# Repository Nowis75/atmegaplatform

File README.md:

# ATmega328P socket-based teaching platform

Firmware examples and supporting material for the paper
*"Design and Implementation of a Jumper-Wire-Free, Socket-Based PCB Platform for Microcontroller Education"* (M. Novak, University of South Bohemia in České Budějovice).

The platform is a two-layer carrier PCB for the ATmega328P (DIP-28, 16 MHz, 5 V). All connections are fixed copper traces. Students insert the functional components into female socket headers: the MCU, crystal, load capacitors, reset network, LEDs, switches and thermistors. No jumper wires are needed.

## Board pin map

| Function | Pins |
|---|---|
| LEDs | D9, D10, D11, D13 (220 Ω series resistors) |
| Switches | D5, D6, D7 (switch to GND, use `INPUT_PULLUP`) |
| NTC thermistor dividers | A0, A1 (10 kΩ NTC to GND, β = 3950; 10 kΩ to VCC) |
| I²C header J1 | VCC, GND, SCL (A5), SDA (A4) |
| UART header UART1 | VCC, GND, RX, TX, DTR, RTS: connect a 5 V CP2102 USB-to-TTL adapter (TX↔RX crossed) |
| Auto-reset | DTR → 1 µF → RESET (automatic reset before upload) |

## Repository structure

```
firmware/
  arduino/      Arduino IDE sketches (open the .ino in each folder)
  platformio/   PlatformIO project, one environment per example
docs/fritzing/  Fritzing wiring diagrams of the exercises (breadboard reference)
hardware/       KiCad schematic and PCB of the carrier board, BOM
data/           Anonymized questionnaire data (to be added)
```

## Programming

The ATmega328P carries an Arduino-compatible (Uno/Optiboot) bootloader. The board connects to the computer through a CP2102 USB-to-TTL adapter, which also powers it from USB.

**Arduino IDE:** select *Arduino Uno* as the board and the CP2102 serial port, then upload.

**PlatformIO / VS Code:**

```bash
cd firmware/platformio
pio run -e 01-led-test -t upload   # build and upload one example
pio device monitor                 # serial monitor, 9600 Bd
```

## Examples

| Topic | Arduino IDE (`firmware/arduino`) | PlatformIO env (`firmware/platformio`) |
|---|---|---|
| Board test, serial | `01-serial-test` | `01-led-test` |
| Digital output | `02-a-led`, `02-b-led-blink` | `01-led-test` |
| Digital input | `02-c-led-button` | `05-a-button-polling` |
| Logic functions | `02-d-logic-gate` | `02-e-logic-function` |
| Serial communication | `03-a-serial-sum`, `03-b-serial-led` | `03-a` … `03-f` |
| EEPROM | `04-eeprom-led` | `04-a-eeprom-led-state`, `04-b-eeprom-sos`, `04-c-eeprom-counter` |
| Interrupts, timers | — | `05-b-button-interrupt`, `05-c-timer-isr` |
| I²C | `06-i2c-vl53l0x` (needs Adafruit_VL53L0X library) | `06-a-i2c-bme280`, `06-b-i2c-scanner` |
| Analog input (NTC) | `07-analog-ntc` | `07-analog-ntc` |

Notes:

- `05-b-button-interrupt` uses external interrupt INT0 on D2, which is not routed to a board switch. Connect a button to D2 or adapt the pin.
- Some PlatformIO examples (`04-*`, `05-a`) were written for breadboard wiring with active-high buttons (`INPUT`, external pull-down). On the PCB, the switches connect to GND. Change these sketches to `INPUT_PULLUP` and test for `LOW`, as the Arduino sketches `02-c-*` already do.

## License

Firmware and hardware design files: MIT (see `LICENSE`).

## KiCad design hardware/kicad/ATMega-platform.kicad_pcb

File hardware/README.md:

# Hardware: carrier PCB (KiCad)

| File | Content |
|---|---|
| `kicad/ATMega-platform.kicad_pro` | KiCad project |
| `kicad/ATMega-platform.kicad_sch` | Schematic |
| `kicad/ATMega-platform.kicad_pcb` | Two-layer PCB layout (1.6 mm) |
| `bom.csv` | Bill of materials |

Gerber and drill files are generated from the `.kicad_pcb` with KiCad's *Fabrication Outputs* (File → Fabrication Outputs → Gerbers / Drill Files).

## Revision notes

- **LED series resistors R2–R5 are 220 Ω.** The first prototype boards used 10 kΩ, which made the LEDs very dim.
- **C3 (1 µF) couples the DTR line of the CP2102 adapter to RESET.** The Arduino IDE / PlatformIO therefore resets the MCU automatically before an upload.
- **The push buttons SW2–SW4 connect D5–D7 to GND.** Use `INPUT_PULLUP` in firmware (pressed = LOW).
- **No dedicated VCC/AVCC decoupling capacitor is fitted.** Adding 100 nF ceramic capacitors at pins 7/8 and 20/22 is recommended for the next revision.
- **The schematic is the current reference (rev. 1.1).** The LED circuits are drawn as MCU pin → 220 Ω → LED → GND. The tactile push buttons SW2–SW4 (6 × 6 mm, symbol `SW_Push`) switch D5–D7 to GND.
- **The `.kicad_pcb` is the layout of the manufactured boards (rev. 1.0).** There the LED sits between the pin and the resistor, the resistor goes to GND, and the silkscreen still shows 10 kΩ for R2–R5. Because all parts are socketed, the boards work with the rev. 1.1 values: insert the LED with its anode toward the MCU pin and use 220 Ω resistors. Run *Tools → Update PCB from Schematic* (F8) and re-route the LED nets before ordering new boards.
- **Board size:** 101 × 48 mm, two copper layers, 1.6 mm FR-4.

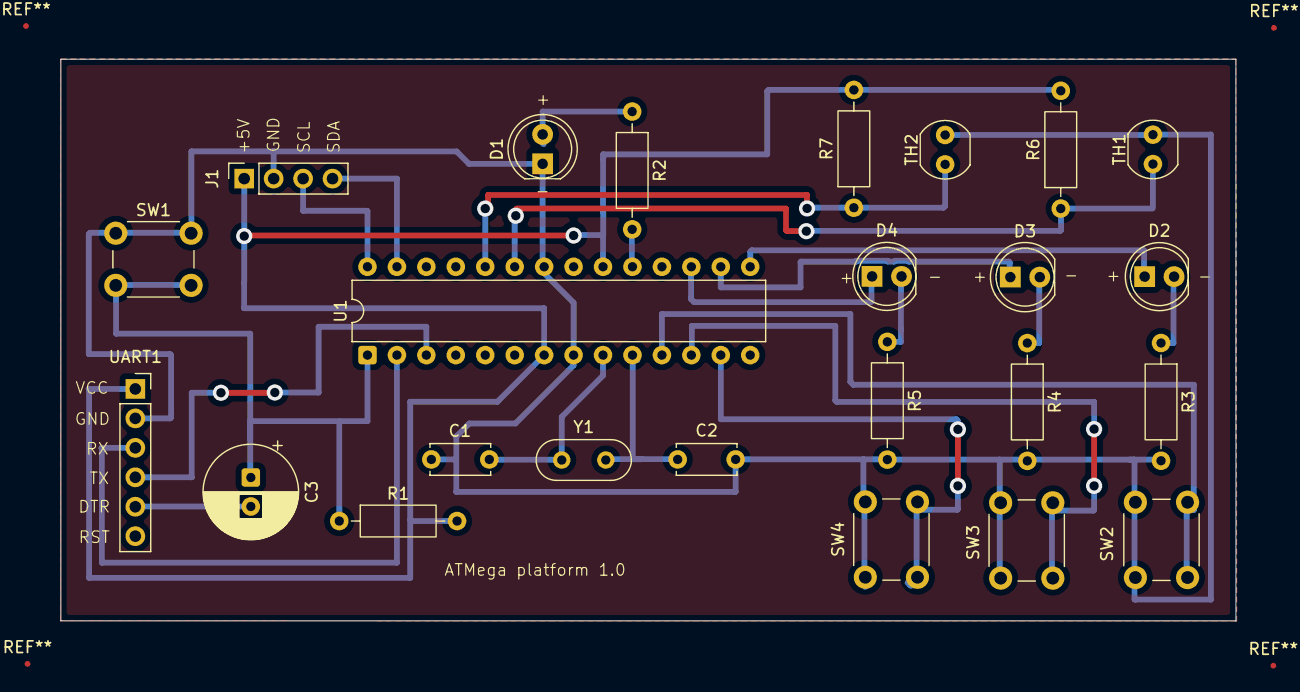
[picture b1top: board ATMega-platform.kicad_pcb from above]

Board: 2 copper layers, 101.4 x 48.5 mm, 24 parts (0 on the bottom side), 23 nets.

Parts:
C1, C2: 22pF; C_Disc_D5.0mm_W2.5mm_P5.00mm
C3: 1uF; CP_Radial_D8.0mm_P2.50mm
D1, D2, D3, D4: LED; LED_D5.0mm
J1: BME280_socket; PinSocket_1x04_P2.54mm_Vertical
R1, R6, R7: 10k; R_Axial_DIN0207_L6.3mm_D2.5mm_P10.16mm_Horizontal
R2, R3, R4, R5: 220; R_Axial_DIN0207_L6.3mm_D2.5mm_P10.16mm_Horizontal
SW1: SW_Push; SW_PUSH_6mm
SW2, SW3, SW4: SW_DIP_x02; SW_PUSH_6mm
TH1, TH2: Thermistor; R_LDR_4.9x4.2mm_P2.54mm_Vertical
U1: ATmega328-P; DIP-28_W7.62mm
UART1: UART_Socket; PinSocket_1x06_P2.54mm_Vertical
Y1: Crystal; Crystal_HC52-6mm_Vertical

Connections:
A0: R6.1, TH1.1, U1.23 (PC0)
A1: R7.1, TH2.1, U1.24 (PC1)
D5: SW2.2, U1.11 (PD5)
D6: SW3.2, U1.12 (PD6)
D7: SW4.2, U1.13 (PD7)
D9: D2.1 (K), U1.15 (PB1)
D10: D3.1 (K), U1.16 (PB2)
D11: D4.1 (K), U1.17 (PB3)
D13: R2.2, U1.19 (PB5)
DTR: C3.2, UART1.5
GND: C1.2, C2.2, D1.1 (K), J1.2, R3.2, R4.2, R5.2, SW1.1, SW2.1, SW3.1, SW4.1, TH1.2, TH2.2, U1.8 (GND), U1.22 (GND), UART1.2
unnamed: D1.2 (A), R2.1
unnamed: D2.2 (A), R3.1
unnamed: D3.2 (A), R4.1
unnamed: D4.2 (A), R5.1
RST: C3.1, R1.1, SW1.2, U1.1 (~RESET/PC6)
RX: U1.2 (PD0), UART1.3
SCL: J1.3, U1.28 (PC5)
SDA: J1.4, U1.27 (PC4)
TX: U1.3 (PD1), UART1.4
VCC: J1.1, R1.2, R6.2, R7.2, U1.7 (VCC), U1.20 (AVCC), UART1.1
XTAL1: C1.1, U1.9 (XTAL1/PB6), Y1.1
XTAL2: C2.1, U1.10 (XTAL2/PB7), Y1.2
